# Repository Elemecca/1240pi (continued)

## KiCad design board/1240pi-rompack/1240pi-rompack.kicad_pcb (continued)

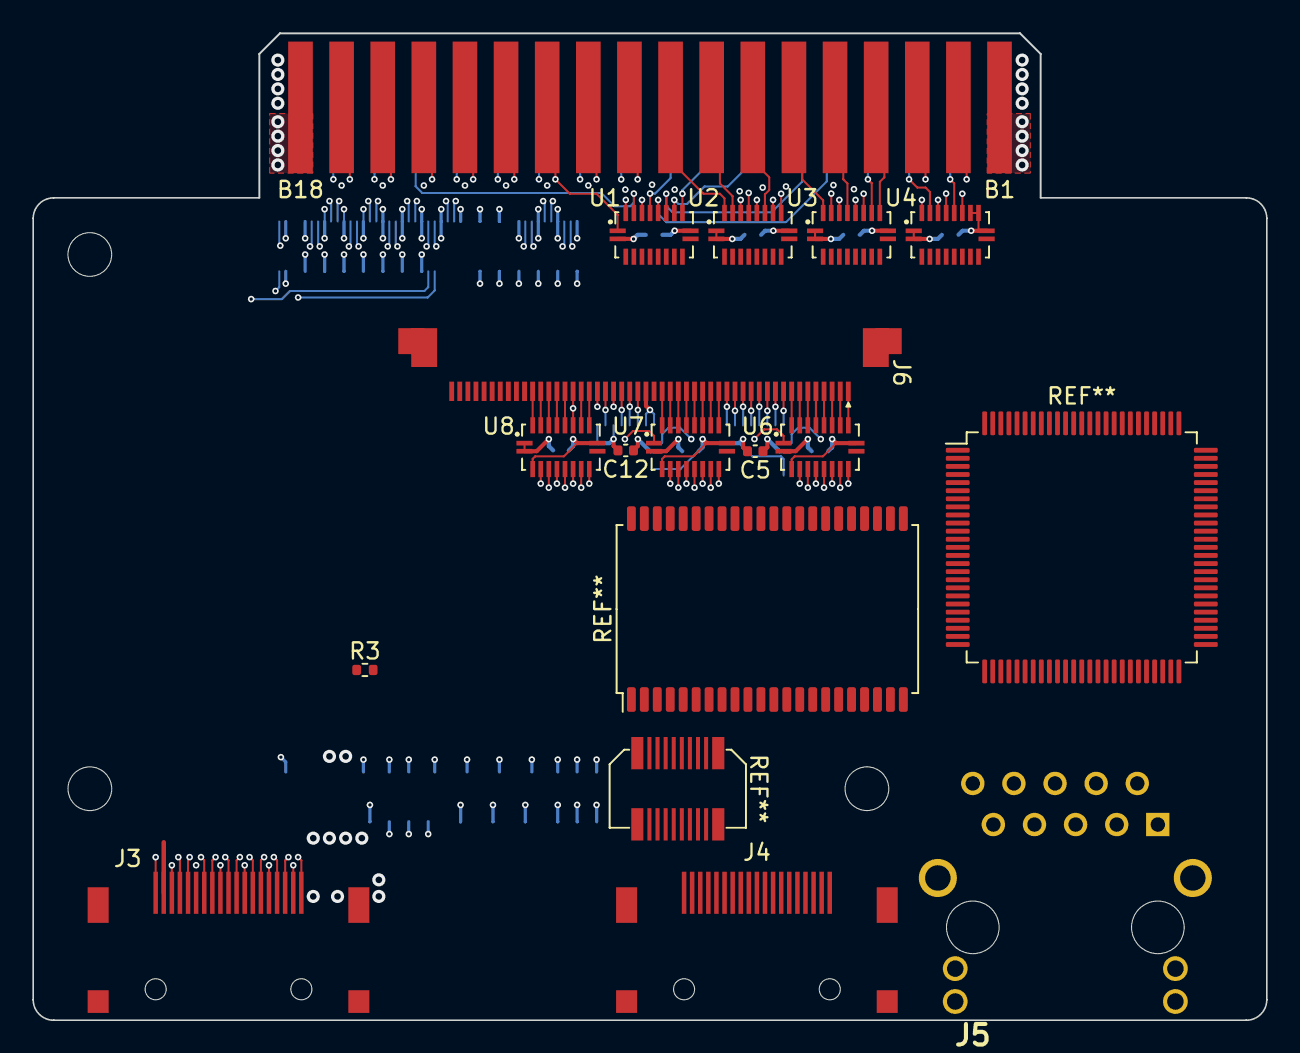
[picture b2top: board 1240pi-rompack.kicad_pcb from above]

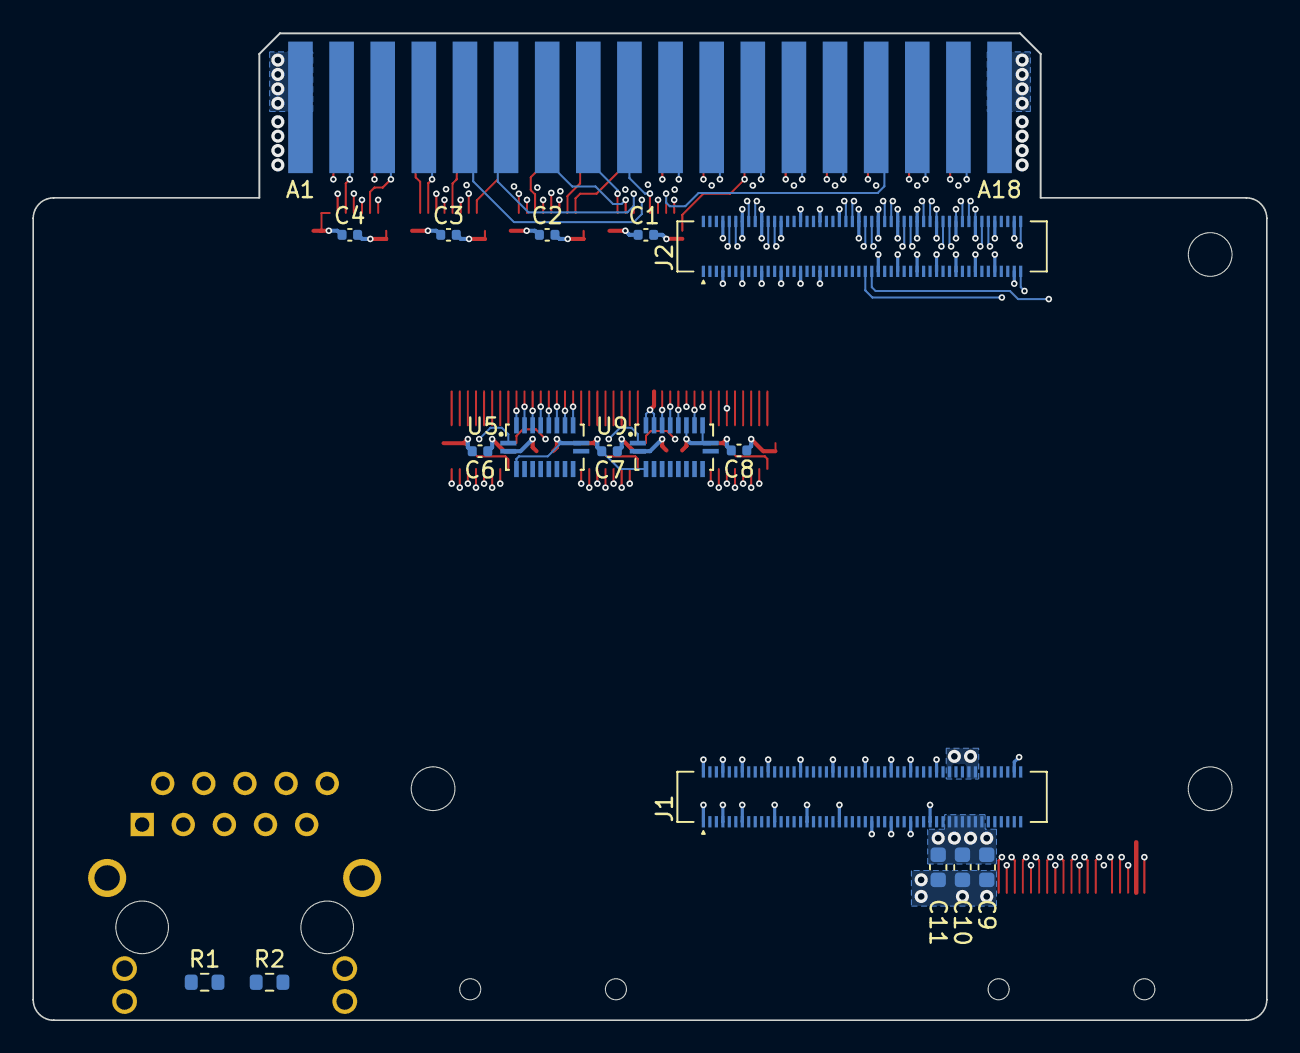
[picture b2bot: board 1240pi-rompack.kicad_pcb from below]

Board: 6 copper layers, 76.2 x 61.0 mm, 34 parts (17 on the bottom side), 95 nets.

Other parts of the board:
MH1, MH1#2, MH1#3: MountingHole_2.7mm_M2.5

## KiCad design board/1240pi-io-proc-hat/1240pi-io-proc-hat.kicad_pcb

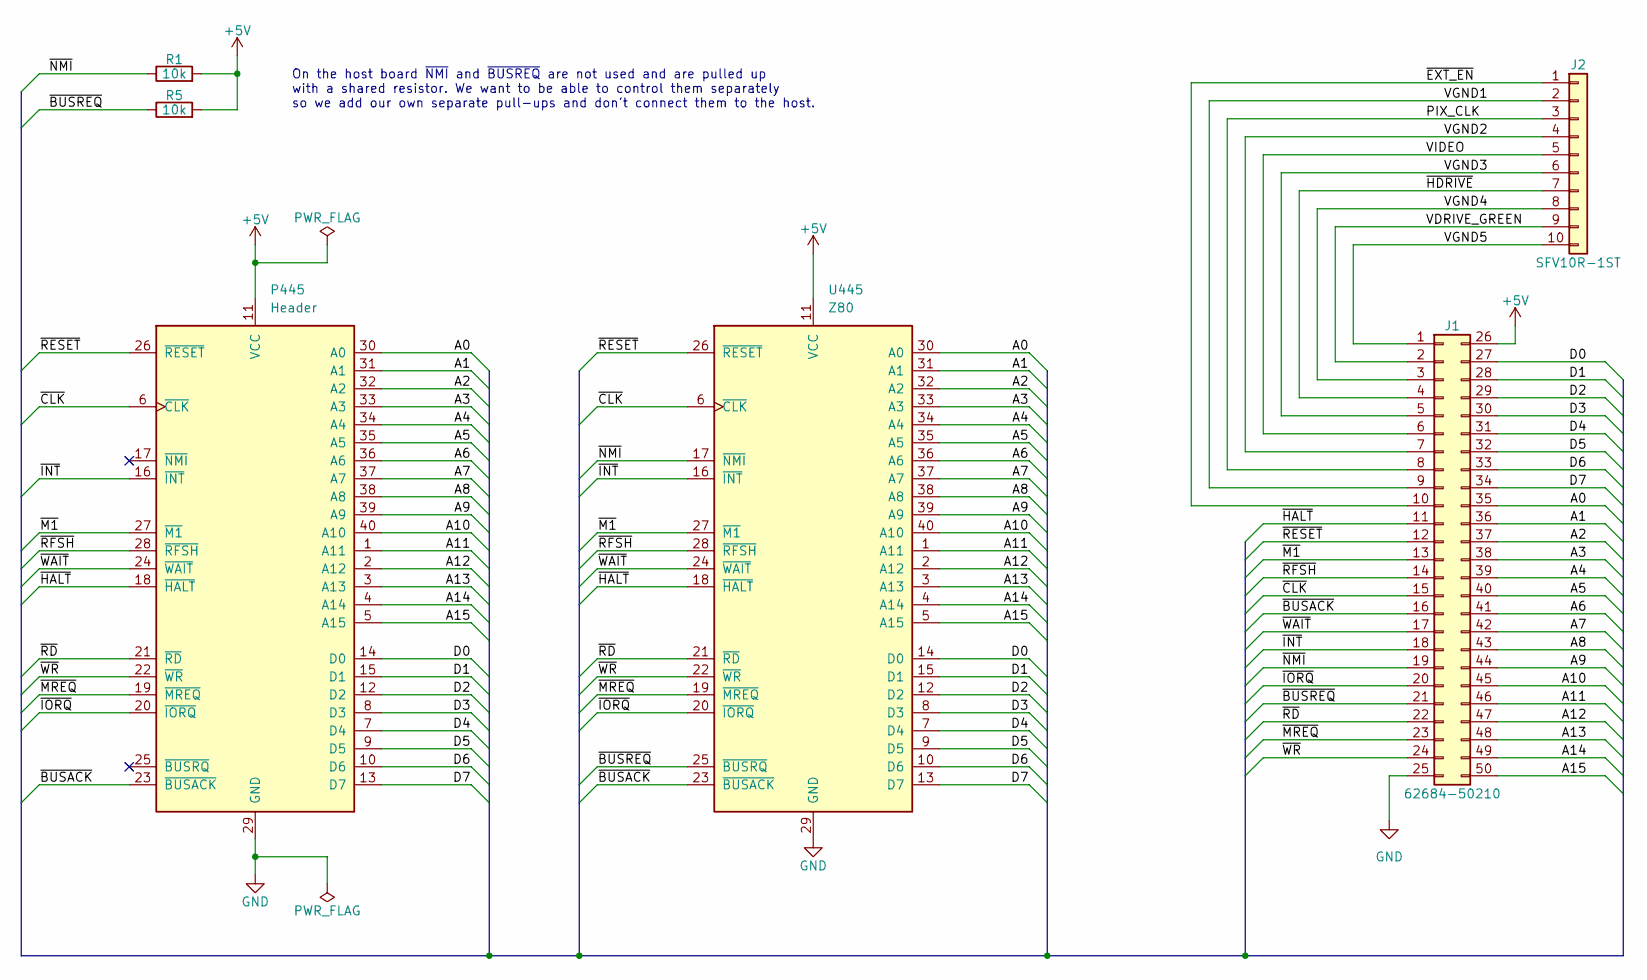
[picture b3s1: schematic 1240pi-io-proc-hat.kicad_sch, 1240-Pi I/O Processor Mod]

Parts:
J1: 62684-50210; Amphenol_62684-50210
J2: SFV10R-1ST; Amphenol_SFV10R-1ST
P445: Header; DIP-40_W15.24mm
R1, R5: 10k; R_0805_2012Metric
U445: Z80; DIP-40_W15.24mm_Socket

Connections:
+5V: J1.26, P445.11 (VCC), R1.2, R5.2, U445.11 (VCC)
/A0: J1.35, P445.30 (A0), U445.30 (A0)
/A1: J1.36, P445.31 (A1), U445.31 (A1)
/A2: J1.37, P445.32 (A2), U445.32 (A2)
/A3: J1.38, P445.33 (A3), U445.33 (A3)
/A4: J1.39, P445.34 (A4), U445.34 (A4)
/A5: J1.40, P445.35 (A5), U445.35 (A5)
/A6: J1.41, P445.36 (A6), U445.36 (A6)
/A7: J1.42, P445.37 (A7), U445.37 (A7)
/A8: J1.43, P445.38 (A8), U445.38 (A8)
/A9: J1.44, P445.39 (A9), U445.39 (A9)
/A10: J1.45, P445.40 (A10), U445.40 (A10)
/A11: J1.46, P445.1 (A11), U445.1 (A11)
/A12: J1.47, P445.2 (A12), U445.2 (A12)
/A13: J1.48, P445.3 (A13), U445.3 (A13)
/A14: J1.49, P445.4 (A14), U445.4 (A14)
/A15: J1.50, P445.5 (A15), U445.5 (A15)
/D0: J1.27, P445.14 (D0), U445.14 (D0)
/D1: J1.28, P445.15 (D1), U445.15 (D1)
/D2: J1.29, P445.12 (D2), U445.12 (D2)
/D3: J1.30, P445.8 (D3), U445.8 (D3)
/D4: J1.31, P445.7 (D4), U445.7 (D4)
/D5: J1.32, P445.9 (D5), U445.9 (D5)
/D6: J1.33, P445.10 (D6), U445.10 (D6)
/D7: J1.34, P445.13 (D7), U445.13 (D7)
/PIX_CLK: J1.8, J2.3
/VDRIVE_GREEN: J1.2, J2.9
/VGND1: J1.9, J2.2
/VGND2: J1.7, J2.4
/VGND3: J1.5, J2.6
/VGND4: J1.3, J2.8
/VGND5: J1.1, J2.10
/VIDEO: J1.6, J2.5
/~BUSACK: J1.16, P445.23 (~BUSACK), U445.23 (~BUSACK)
/~BUSREQ: J1.21, R5.1, U445.25 (~BUSRQ)
/~CLK: J1.15, P445.6 (~CLK), U445.6 (~CLK)
/~EXT_EN: J1.10, J2.1
/~HALT: J1.11, P445.18 (~HALT), U445.18 (~HALT)
/~HDRIVE: J1.4, J2.7
/~INT: J1.18, P445.16 (~INT), U445.16 (~INT)
/~IORQ: J1.20, P445.20 (~IORQ), U445.20 (~IORQ)
/~M1: J1.13, P445.27 (~M1), U445.27 (~M1)
/~MREQ: J1.23, P445.19 (~MREQ), U445.19 (~MREQ)
/~NMI: J1.19, R1.1, U445.17 (~NMI)
/~RD: J1.22, P445.21 (~RD), U445.21 (~RD)
/~RESET: J1.12, P445.26 (~RESET), U445.26 (~RESET)
/~RFSH: J1.14, P445.28 (~RFSH), U445.28 (~RFSH)
/~WAIT: J1.17, P445.24 (~WAIT), U445.24 (~WAIT)
/~WR: J1.24, P445.22 (~WR), U445.22 (~WR)
GND: J1.25, P445.29 (GND), U445.29 (GND)

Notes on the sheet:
On the host board ~{NMI} and ~{BUSREQ} are not used and are pulled up with a shared resistor. We want to be able to control them separately so we add our own separate pull-ups and don't connect them to the host.

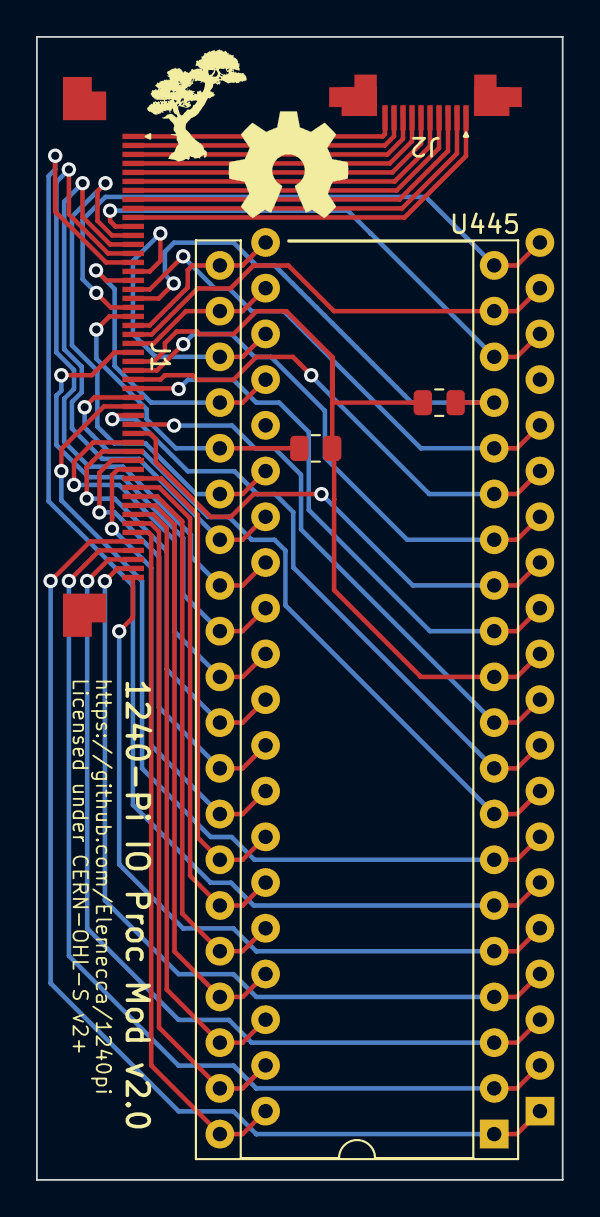
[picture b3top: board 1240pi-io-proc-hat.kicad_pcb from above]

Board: 2 copper layers, 29.2 x 63.5 mm, 6 parts (0 on the bottom side), 50 nets.

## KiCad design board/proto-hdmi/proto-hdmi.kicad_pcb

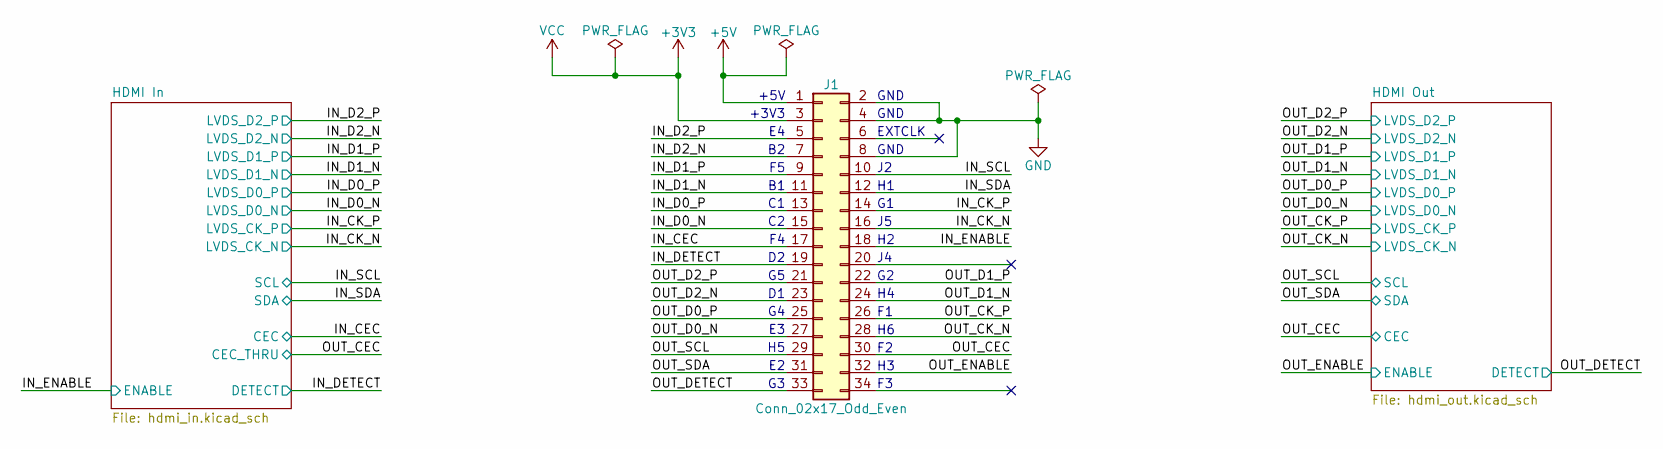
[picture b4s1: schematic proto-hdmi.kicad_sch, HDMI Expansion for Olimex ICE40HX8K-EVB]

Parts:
J1: Conn_02x17_Odd_Even; PinSocket_2x17_P2.54mm_Horizontal

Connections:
+3V3: J1.3; also elsewhere on the board
+5V: J1.1; also elsewhere on the board
/IN_CEC: J1.17; also elsewhere on the board
/IN_CK_N: J1.16; also elsewhere on the board
/IN_CK_P: J1.14; also elsewhere on the board
/IN_D0_N: J1.15; also elsewhere on the board
/IN_D0_P: J1.13; also elsewhere on the board
/IN_D1_N: J1.11; also elsewhere on the board
/IN_D1_P: J1.9; also elsewhere on the board
/IN_D2_N: J1.7; also elsewhere on the board
/IN_D2_P: J1.5; also elsewhere on the board
/IN_DETECT: J1.19; also elsewhere on the board
/IN_ENABLE: J1.18; also elsewhere on the board
/IN_SCL: J1.10; also elsewhere on the board
/IN_SDA: J1.12; also elsewhere on the board
/OUT_CEC: J1.30; also elsewhere on the board
/OUT_CK_N: J1.28; also elsewhere on the board
/OUT_CK_P: J1.26; also elsewhere on the board
/OUT_D0_N: J1.27; also elsewhere on the board
/OUT_D0_P: J1.25; also elsewhere on the board
/OUT_D1_N: J1.24; also elsewhere on the board
/OUT_D1_P: J1.22; also elsewhere on the board
/OUT_D2_N: J1.23; also elsewhere on the board
/OUT_D2_P: J1.21; also elsewhere on the board
/OUT_DETECT: J1.33; also elsewhere on the board
/OUT_ENABLE: J1.32; also elsewhere on the board
/OUT_SCL: J1.29; also elsewhere on the board
/OUT_SDA: J1.31; also elsewhere on the board
GND: J1.2, J1.4, J1.8; also elsewhere on the board

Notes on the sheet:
GND
+3V3
EXTCLK
+5V

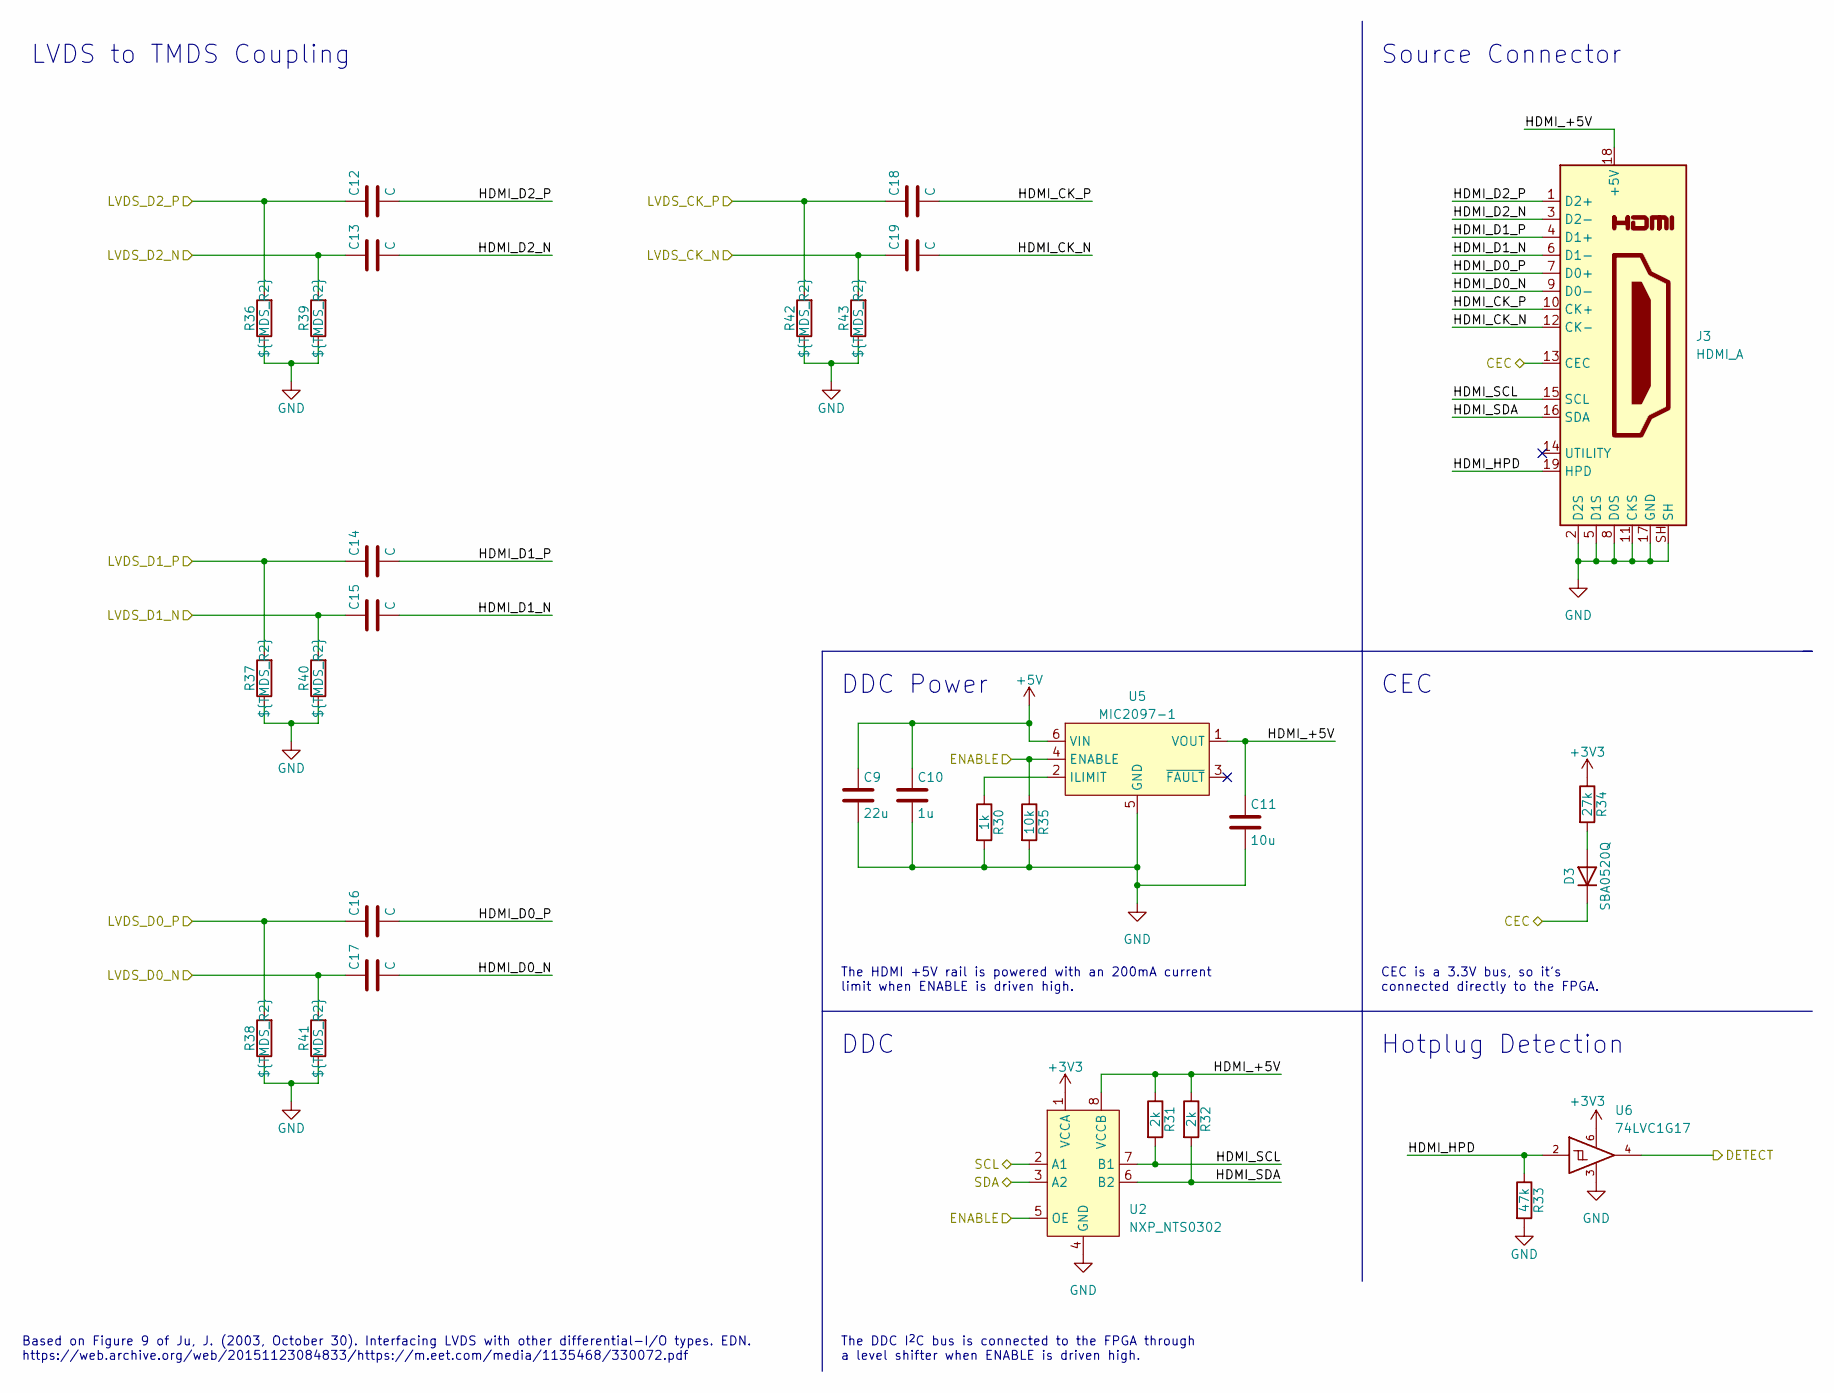
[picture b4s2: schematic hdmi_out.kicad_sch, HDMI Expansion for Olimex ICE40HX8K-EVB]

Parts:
C9: 22u; C_0402_1005Metric
C10: 1u; C_0402_1005Metric
C11: 10u; C_0402_1005Metric
C12, C13, C14, C15, C16, C17, C18, C19: C; C_0402_1005Metric
D3: SBA0520Q; D_0402_1005Metric
J3: HDMI_A; CNC_2000-1-2-41-00-BK
R30: 1k; R_0402_1005Metric
R31, R32: 2k; R_0402_1005Metric
R33: 47k; R_0402_1005Metric
R34: 27k; R_0402_1005Metric
R35: 10k; R_0402_1005Metric
R36, R37, R38, R39, R40, R41, R42, R43: ${TMDS_R2}; R_0402_1005Metric
U2: NXP_NTS0302; X2SON-8_1.4x1mm_P0.35mm
U5: MIC2097-1; Package_TMLF-6_EP_1.6mm
U6: 74LVC1G17; SOT-886

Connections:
+3V3: R34.1, U2.1 (VCCA), U6.6; also elsewhere on the board
+5V: C9.1, C10.1, U5.6 (VIN); also elsewhere on the board
/HDMI Out/HDMI_+5V: C11.1, J3.18 (+5V), R31.1, R32.1, U2.8 (VCCB), U5.1 (VOUT)
/HDMI Out/HDMI_CK_N: C19.2, J3.12 (CK-)
/HDMI Out/HDMI_CK_P: C18.2, J3.10 (CK+)
/HDMI Out/HDMI_D0_N: C17.2, J3.9 (D0-)
/HDMI Out/HDMI_D0_P: C16.2, J3.7 (D0+)
/HDMI Out/HDMI_D1_N: C15.2, J3.6 (D1-)
/HDMI Out/HDMI_D1_P: C14.2, J3.4 (D1+)
/HDMI Out/HDMI_D2_N: C13.2, J3.3 (D2-)
/HDMI Out/HDMI_D2_P: C12.2, J3.1 (D2+)
/HDMI Out/HDMI_HPD: J3.19 (HPD), R33.1, U6.2
/HDMI Out/HDMI_SCL: J3.15 (SCL), R31.2, U2.7 (B1)
/HDMI Out/HDMI_SDA: J3.16 (SDA), R32.2, U2.6 (B2)
/OUT_CEC: D3.1 (K), J3.13 (CEC); also elsewhere on the board
/OUT_CK_N: C19.1, R43.2; also elsewhere on the board
/OUT_CK_P: C18.1, R42.2; also elsewhere on the board
/OUT_D0_N: C17.1, R41.2; also elsewhere on the board
/OUT_D0_P: C16.1, R38.2; also elsewhere on the board
/OUT_D1_N: C15.1, R40.2; also elsewhere on the board
/OUT_D1_P: C14.1, R37.2; also elsewhere on the board
/OUT_D2_N: C13.1, R39.2; also elsewhere on the board
/OUT_D2_P: C12.1, R36.2; also elsewhere on the board
/OUT_DETECT: U6.4; also elsewhere on the board
/OUT_ENABLE: R35.1, U2.5 (OE), U5.4 (ENABLE); also elsewhere on the board
/OUT_SCL: U2.2 (A1); also elsewhere on the board
/OUT_SDA: U2.3 (A2); also elsewhere on the board
GND: C9.2, C10.2, C11.2, J3.2 (D2S), J3.5 (D1S), J3.8 (D0S), J3.11 (CKS), J3.17 (GND), J3.SH, R30.2, R33.2, R35.2, R36.1, R37.1, R38.1, R39.1, R40.1, R41.1, R42.1, R43.1, U2.4 (GND), U5.5 (GND), U5.EP, U6.3; also elsewhere on the board
unnamed: D3.2 (A), R34.2
unnamed: R30.1, U5.2 (ILIMIT)

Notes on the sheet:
LVDS to TMDS Coupling
Based on Figure 9 of Ju, J. (2003, October 30). Interfacing LVDS with other differential-I/O types. EDN. https://web.archive.org/web/20151123084833/https://m.eet.com/media/1135468/330072.pdf
Hotplug Detection
DDC
DDC Power
Source Connector
The HDMI +5V rail is powered with an 200mA current limit when ENABLE is driven high.
The DDC I^{2}C bus is connected to the FPGA through a level shifter when ENABLE is driven high.
CEC is a 3.3V bus, so it's connected directly to the FPGA.
CEC

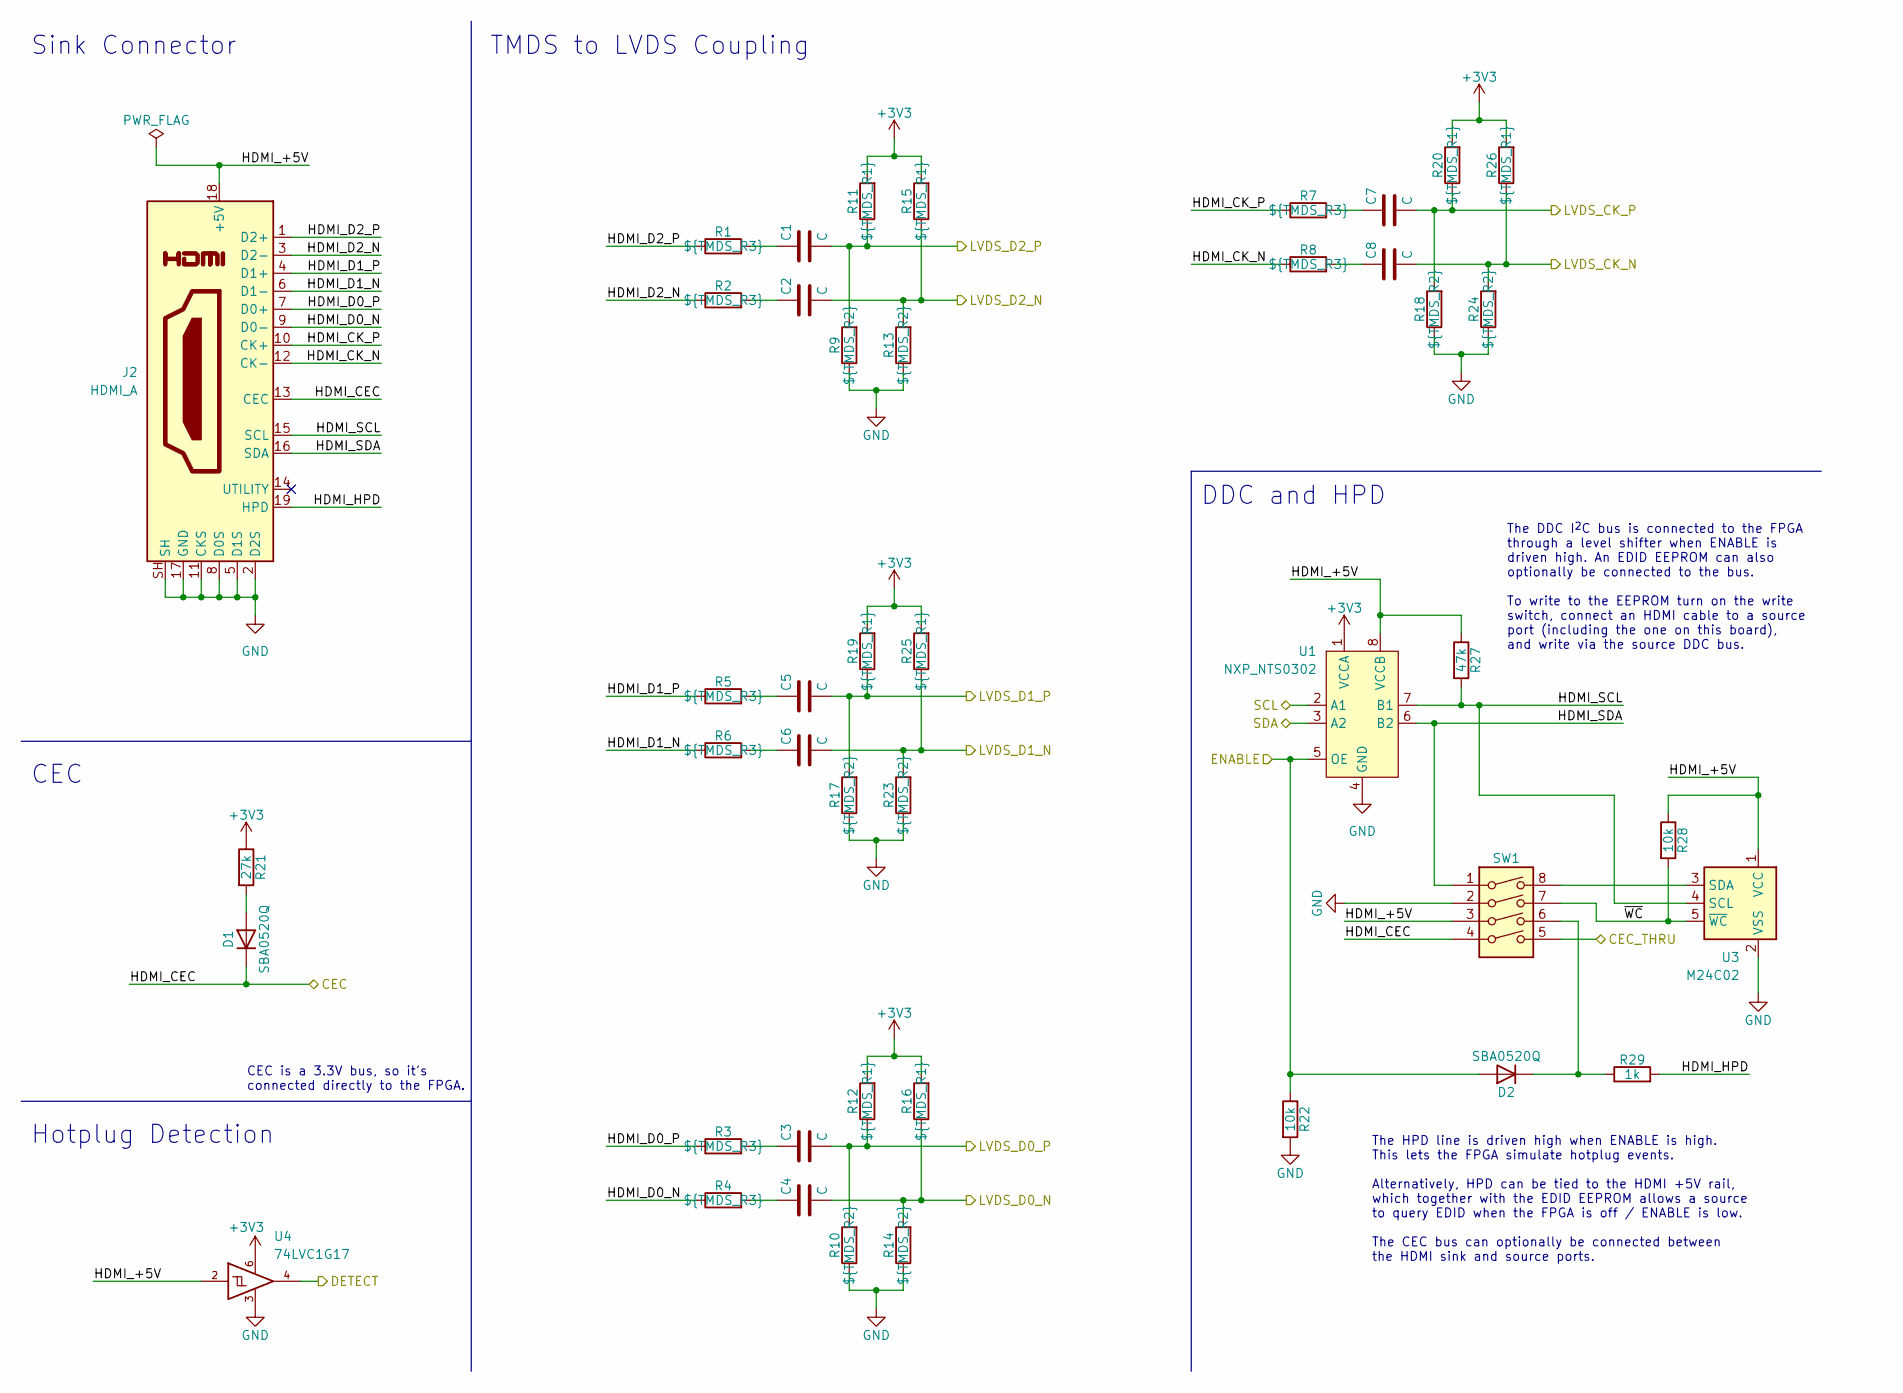
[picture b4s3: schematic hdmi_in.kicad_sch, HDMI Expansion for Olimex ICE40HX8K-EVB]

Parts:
C1, C2, C3, C4, C5, C6, C7, C8: C; C_0402_1005Metric
D1, D2: SBA0520Q; D_0402_1005Metric
J2: HDMI_A; CNC_2000-1-2-41-00-BK
R1, R2, R3, R4, R5, R6, R7, R8: ${TMDS_R3}; R_0402_1005Metric
R9, R10, R13, R14, R17, R18, R23, R24: ${TMDS_R2}; R_0402_1005Metric
R11, R12, R15, R16, R19, R20, R25, R26: ${TMDS_R1}; R_0402_1005Metric
R21: 27k; R_0402_1005Metric
R22, R28: 10k; R_0402_1005Metric
R27: 47k; R_0402_1005Metric
R29: 1k; R_0402_1005Metric
SW1: CTS_218-4LPSTR; CTS_218-4
U1: NXP_NTS0302; X2SON-8_1.4x1mm_P0.35mm
U3: M24C02; ST_UFDFPN5
U4: 74LVC1G17; SOT-886

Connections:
+3V3: R11.2, R12.2, R15.2, R16.2, R19.2, R20.2, R21.1, R25.2, R26.2, U1.1 (VCCA), U4.6; also elsewhere on the board
/HDMI In/HDMI_+5V: J2.18 (+5V), R27.1, R28.1, SW1.3, U1.8 (VCCB), U3.1 (VCC), U4.2
/HDMI In/HDMI_CK_N: J2.12 (CK-), R8.1
/HDMI In/HDMI_CK_P: J2.10 (CK+), R7.1
/HDMI In/HDMI_D0_N: J2.9 (D0-), R4.1
/HDMI In/HDMI_D0_P: J2.7 (D0+), R3.1
/HDMI In/HDMI_D1_N: J2.6 (D1-), R6.1
/HDMI In/HDMI_D1_P: J2.4 (D1+), R5.1
/HDMI In/HDMI_D2_N: J2.3 (D2-), R2.1
/HDMI In/HDMI_D2_P: J2.1 (D2+), R1.1
/HDMI In/HDMI_HPD: J2.19 (HPD), R29.2
/HDMI In/HDMI_SCL: J2.15 (SCL), R27.2, U1.7 (B1), U3.4 (SCL)
/HDMI In/HDMI_SDA: J2.16 (SDA), SW1.1, U1.6 (B2)
/HDMI In/~WC: R28.2, SW1.7, U3.5 (~WC)
/IN_CEC: D1.1 (K), J2.13 (CEC), SW1.4; also elsewhere on the board
/IN_CK_N: C8.2, R24.2, R26.1; also elsewhere on the board
/IN_CK_P: C7.2, R18.2, R20.1; also elsewhere on the board
/IN_D0_N: C4.2, R14.2, R16.1; also elsewhere on the board
/IN_D0_P: C3.2, R10.2, R12.1; also elsewhere on the board
/IN_D1_N: C6.2, R23.2, R25.1; also elsewhere on the board
/IN_D1_P: C5.2, R17.2, R19.1; also elsewhere on the board
/IN_D2_N: C2.2, R13.2, R15.1; also elsewhere on the board
/IN_D2_P: C1.2, R9.2, R11.1; also elsewhere on the board
/IN_DETECT: U4.4; also elsewhere on the board
/IN_ENABLE: D2.2 (A), R22.1, U1.5 (OE); also elsewhere on the board
/IN_SCL: U1.2 (A1); also elsewhere on the board
/IN_SDA: U1.3 (A2); also elsewhere on the board
/OUT_CEC: SW1.5; also elsewhere on the board
GND: J2.2 (D2S), J2.5 (D1S), J2.8 (D0S), J2.11 (CKS), J2.17 (GND), J2.SH, R9.1, R10.1, R13.1, R14.1, R17.1, R18.1, R22.2, R23.1, R24.1, SW1.2, U1.4 (GND), U3.2 (VSS), U4.3; also elsewhere on the board
unnamed: C1.1, R1.2
unnamed: C2.1, R2.2
unnamed: C3.1, R3.2
unnamed: C4.1, R4.2
unnamed: C5.1, R5.2
unnamed: C6.1, R6.2
unnamed: C7.1, R7.2
unnamed: C8.1, R8.2
unnamed: D1.2 (A), R21.2
unnamed: D2.1 (K), R29.1, SW1.6
unnamed: SW1.8, U3.3 (SDA)

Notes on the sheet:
DDC and HPD
TMDS to LVDS Coupling
CEC
CEC is a 3.3V bus, so it's connected directly to the FPGA.
The DDC I^{2}C bus is connected to the FPGA through a level shifter when ENABLE is driven high. An EDID EEPROM can also optionally be connected to the bus. To write to the EEPROM turn on the write switch, connect an HDMI cable to a source port (including the one on this board), and write via the so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
Sink Connector
The HPD line is driven high when ENABLE is high. This lets the FPGA simulate hotplug events. Alternatively, HPD can be tied to the HDMI +5V rail, which together with the EDID EEPROM allows a source to query EDID when the FPGA is off / ENABLE is low. The CEC bus can optionally be connected between t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
Hotplug Detection

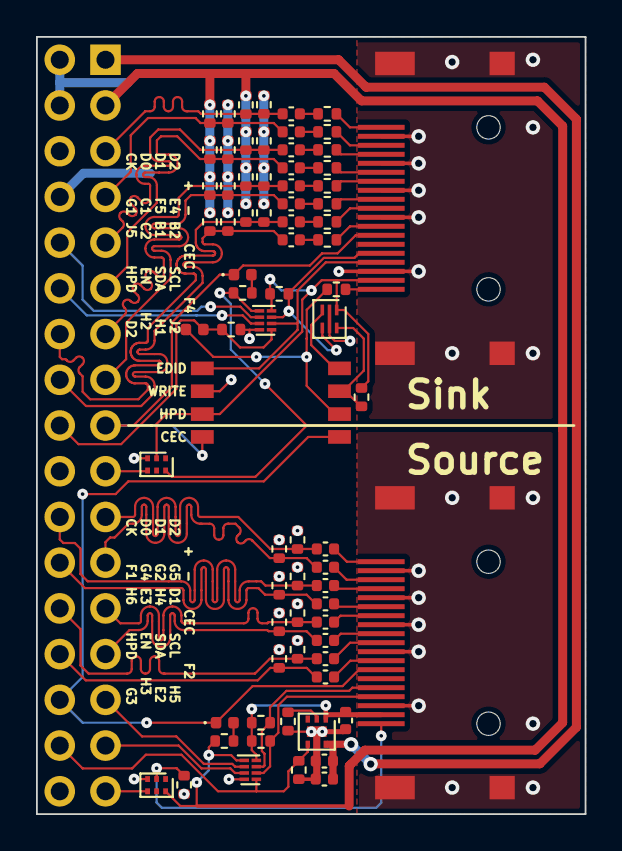
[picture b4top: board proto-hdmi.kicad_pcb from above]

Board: 2 copper layers, 30.5 x 43.2 mm, 75 parts (0 on the bottom side), 67 nets.

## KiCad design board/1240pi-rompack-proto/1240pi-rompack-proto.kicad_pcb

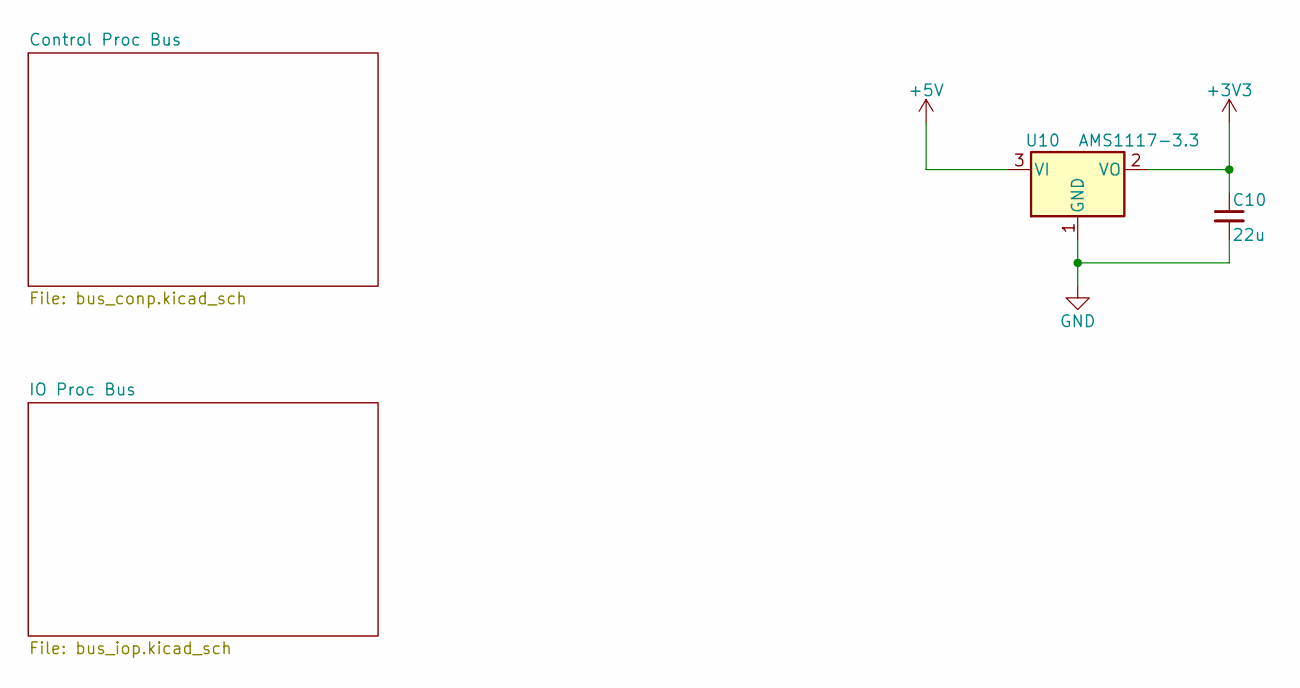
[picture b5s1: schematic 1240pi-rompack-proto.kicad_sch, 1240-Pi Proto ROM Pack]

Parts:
C10: 22u; C_0805_2012Metric
U10: AMS1117-3.3; SOT-223-3_TabPin2

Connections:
+3V3: C10.1, U10.2 (VO); also elsewhere on the board
+5V: U10.3 (VI); also elsewhere on the board

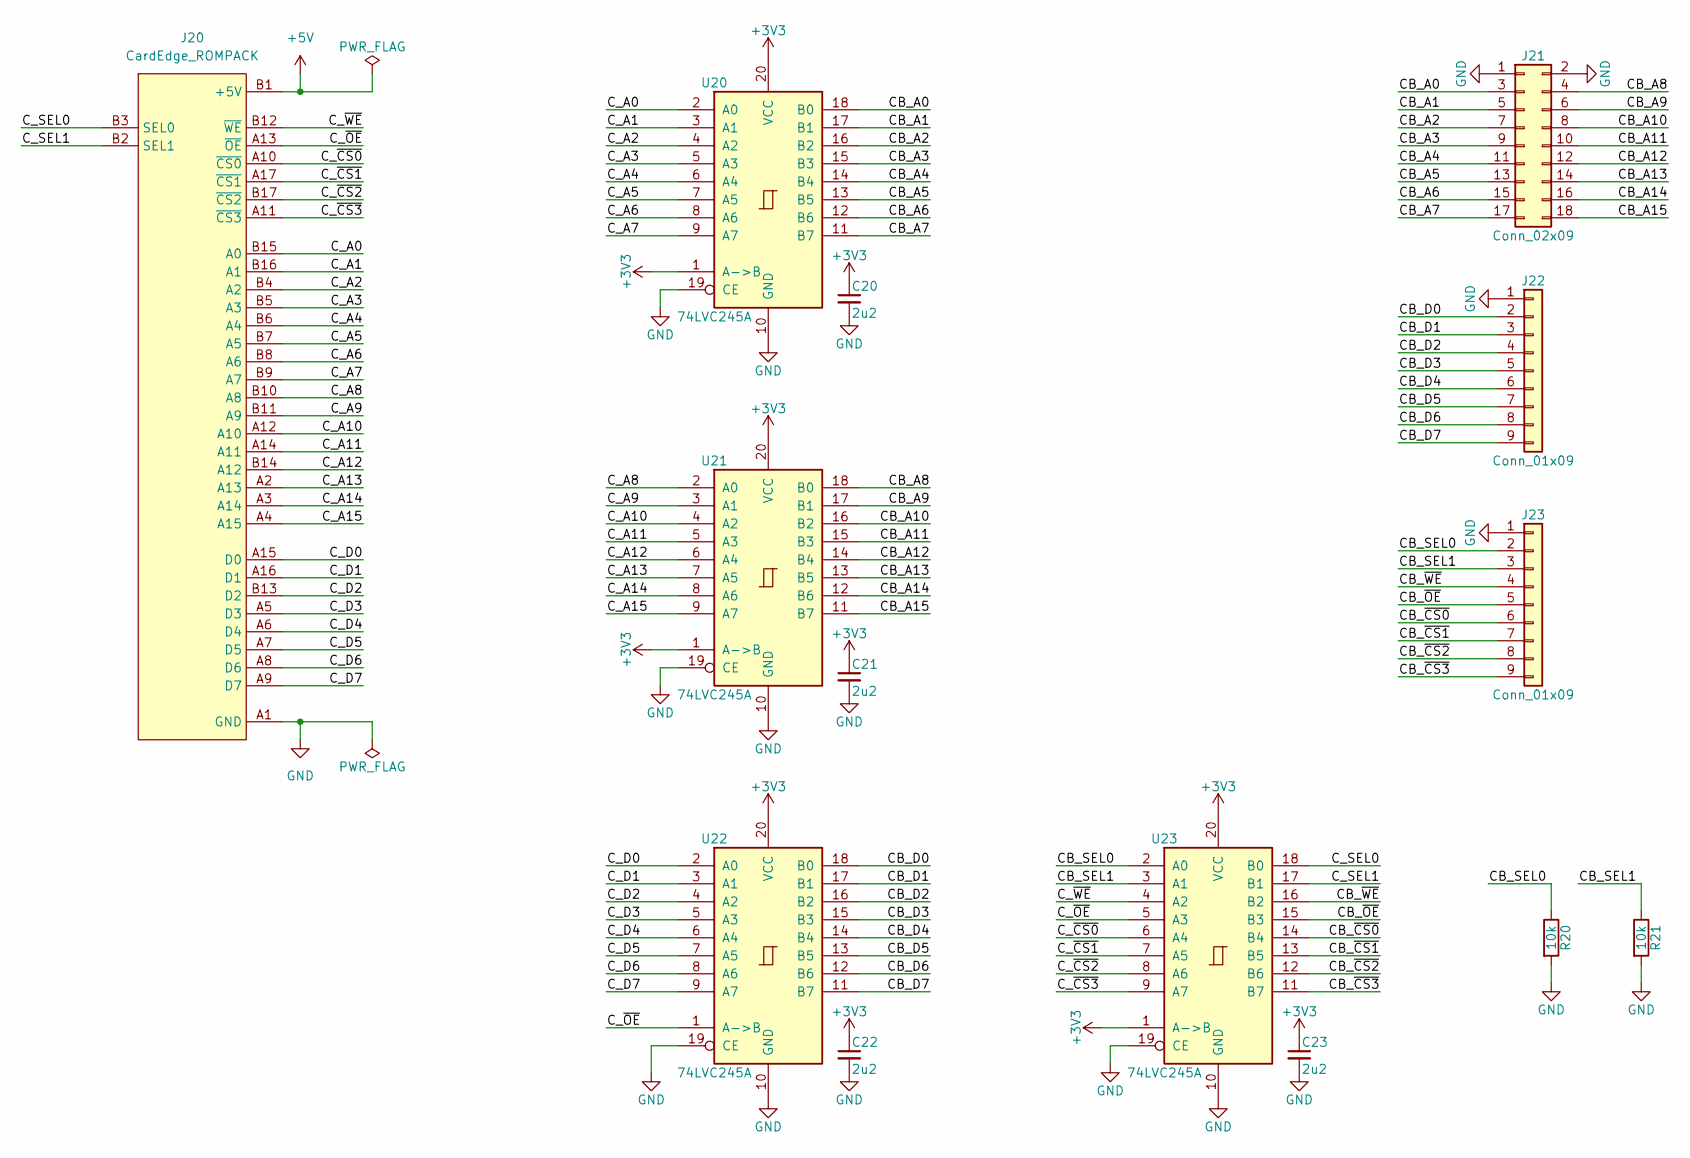
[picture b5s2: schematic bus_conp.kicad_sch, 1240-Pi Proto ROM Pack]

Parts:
C20, C21, C22, C23: 2u2; C_0603_1608Metric
J20: CardEdge_ROMPACK; CardEdge_18x2
J21: Conn_02x09; PinHeader_2x09_P2.54mm_Vertical
J22, J23: Conn_01x09; PinHeader_1x09_P2.54mm_Vertical
R20, R21: 10k; R_0603_1608Metric
U20, U21, U22, U23: 74LVC245A; TSSOP-20_4.4x6.5mm_P0.65mm

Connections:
+3V3: C20.1, C21.1, C22.1, C23.1, U20.1 (A->B), U20.20 (VCC), U21.1 (A->B), U21.20 (VCC), U22.20 (VCC), U23.1 (A->B), U23.20 (VCC); also elsewhere on the board
+5V: J20.B1 (+5V), J20.B18 (+5V); also elsewhere on the board
/Control Proc Bus/CB_A0: J21.3, U20.18 (B0)
/Control Proc Bus/CB_A1: J21.5, U20.17 (B1)
/Control Proc Bus/CB_A2: J21.7, U20.16 (B2)
/Control Proc Bus/CB_A3: J21.9, U20.15 (B3)
/Control Proc Bus/CB_A4: J21.11, U20.14 (B4)
/Control Proc Bus/CB_A5: J21.13, U20.13 (B5)
/Control Proc Bus/CB_A6: J21.15, U20.12 (B6)
/Control Proc Bus/CB_A7: J21.17, U20.11 (B7)
/Control Proc Bus/CB_A8: J21.4, U21.18 (B0)
/Control Proc Bus/CB_A9: J21.6, U21.17 (B1)
/Control Proc Bus/CB_A10: J21.8, U21.16 (B2)
/Control Proc Bus/CB_A11: J21.10, U21.15 (B3)
/Control Proc Bus/CB_A12: J21.12, U21.14 (B4)
/Control Proc Bus/CB_A13: J21.14, U21.13 (B5)
/Control Proc Bus/CB_A14: J21.16, U21.12 (B6)
/Control Proc Bus/CB_A15: J21.18, U21.11 (B7)
/Control Proc Bus/CB_D0: J22.2, U22.18 (B0)
/Control Proc Bus/CB_D1: J22.3, U22.17 (B1)
/Control Proc Bus/CB_D2: J22.4, U22.16 (B2)
/Control Proc Bus/CB_D3: J22.5, U22.15 (B3)
/Control Proc Bus/CB_D4: J22.6, U22.14 (B4)
/Control Proc Bus/CB_D5: J22.7, U22.13 (B5)
/Control Proc Bus/CB_D6: J22.8, U22.12 (B6)
/Control Proc Bus/CB_D7: J22.9, U22.11 (B7)
/Control Proc Bus/CB_SEL0: J23.2, R20.1, U23.2 (A0)
/Control Proc Bus/CB_SEL1: J23.3, R21.1, U23.3 (A1)
/Control Proc Bus/CB_~CS0: J23.6, U23.14 (B4)
/Control Proc Bus/CB_~CS1: J23.7, U23.13 (B5)
/Control Proc Bus/CB_~CS2: J23.8, U23.12 (B6)
/Control Proc Bus/CB_~CS3: J23.9, U23.11 (B7)
/Control Proc Bus/CB_~OE: J23.5, U23.15 (B3)
/Control Proc Bus/CB_~WE: J23.4, U23.16 (B2)
/Control Proc Bus/C_A0: J20.B15 (A0), U20.2 (A0)
/Control Proc Bus/C_A1: J20.B16 (A1), U20.3 (A1)
/Control Proc Bus/C_A2: J20.B4 (A2), U20.4 (A2)
/Control Proc Bus/C_A3: J20.B5 (A3), U20.5 (A3)
/Control Proc Bus/C_A4: J20.B6 (A4), U20.6 (A4)
/Control Proc Bus/C_A5: J20.B7 (A5), U20.7 (A5)
/Control Proc Bus/C_A6: J20.B8 (A6), U20.8 (A6)
/Control Proc Bus/C_A7: J20.B9 (A7), U20.9 (A7)
/Control Proc Bus/C_A8: J20.B10 (A8), U21.2 (A0)
/Control Proc Bus/C_A9: J20.B11 (A9), U21.3 (A1)
/Control Proc Bus/C_A10: J20.A12 (A10), U21.4 (A2)
/Control Proc Bus/C_A11: J20.A14 (A11), U21.5 (A3)
/Control Proc Bus/C_A12: J20.B14 (A12), U21.6 (A4)
/Control Proc Bus/C_A13: J20.A2 (A13), U21.7 (A5)
/Control Proc Bus/C_A14: J20.A3 (A14), U21.8 (A6)
/Control Proc Bus/C_A15: J20.A4 (A15), U21.9 (A7)
/Control Proc Bus/C_D0: J20.A15 (D0), U22.2 (A0)
/Control Proc Bus/C_D1: J20.A16 (D1), U22.3 (A1)
/Control Proc Bus/C_D2: J20.B13 (D2), U22.4 (A2)
/Control Proc Bus/C_D3: J20.A5 (D3), U22.5 (A3)
/Control Proc Bus/C_D4: J20.A6 (D4), U22.6 (A4)
/Control Proc Bus/C_D5: J20.A7 (D5), U22.7 (A5)
/Control Proc Bus/C_D6: J20.A8 (D6), U22.8 (A6)
/Control Proc Bus/C_D7: J20.A9 (D7), U22.9 (A7)
/Control Proc Bus/C_SEL0: J20.B3 (SEL0), U23.18 (B0)
/Control Proc Bus/C_SEL1: J20.B2 (SEL1), U23.17 (B1)
/Control Proc Bus/C_~CS0: J20.A10 (~CS0), U23.6 (A4)
/Control Proc Bus/C_~CS1: J20.A17 (~CS1), U23.7 (A5)
/Control Proc Bus/C_~CS2: J20.B17 (~CS2), U23.8 (A6)
/Control Proc Bus/C_~CS3: J20.A11 (~CS3), U23.9 (A7)
/Control Proc Bus/C_~OE: J20.A13 (~OE), U22.1 (A->B), U23.5 (A3)
/Control Proc Bus/C_~WE: J20.B12 (~WE), U23.4 (A2)
